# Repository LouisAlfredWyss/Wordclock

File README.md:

# Wordclock

Description and code of my Swiss-German Wordclock.

This project uses a Raspberry Pi to control a matrix of 121 WS281x LEDs (NeoPixels). It displays the current time using illuminated words in Swiss-German dialect (e.g., "Es isch viertel vor drüü").

The repository contains the Python code required to drive the LED matrix, as well as the mechanical and electrical files needed to physically build the clock (PCB layouts and laser cutting templates in the `mechanics/` folder).

## Hardware
* Raspberry Pi
* WS281x LED Strip (121 LEDs)
* Custom PCB and laser-cut casing

## Requirements
The project relies on the `rpi_ws281x` and `numpy` Python libraries.

```bash
sudo pip3 install rpi_ws281x numpy
```

## Running the Application
The `rpi_ws281x` library uses PWM via GPIO pin 18 by default, which requires root privileges.

To run the clock, execute the script in the `src/` folder:

```bash
sudo python3 src/main.py
```

### Options
* `-c` or `--clear`: Clears the LED display when the script exits (e.g., via Ctrl+C).

```bash
sudo python3 src/main.py -c
```

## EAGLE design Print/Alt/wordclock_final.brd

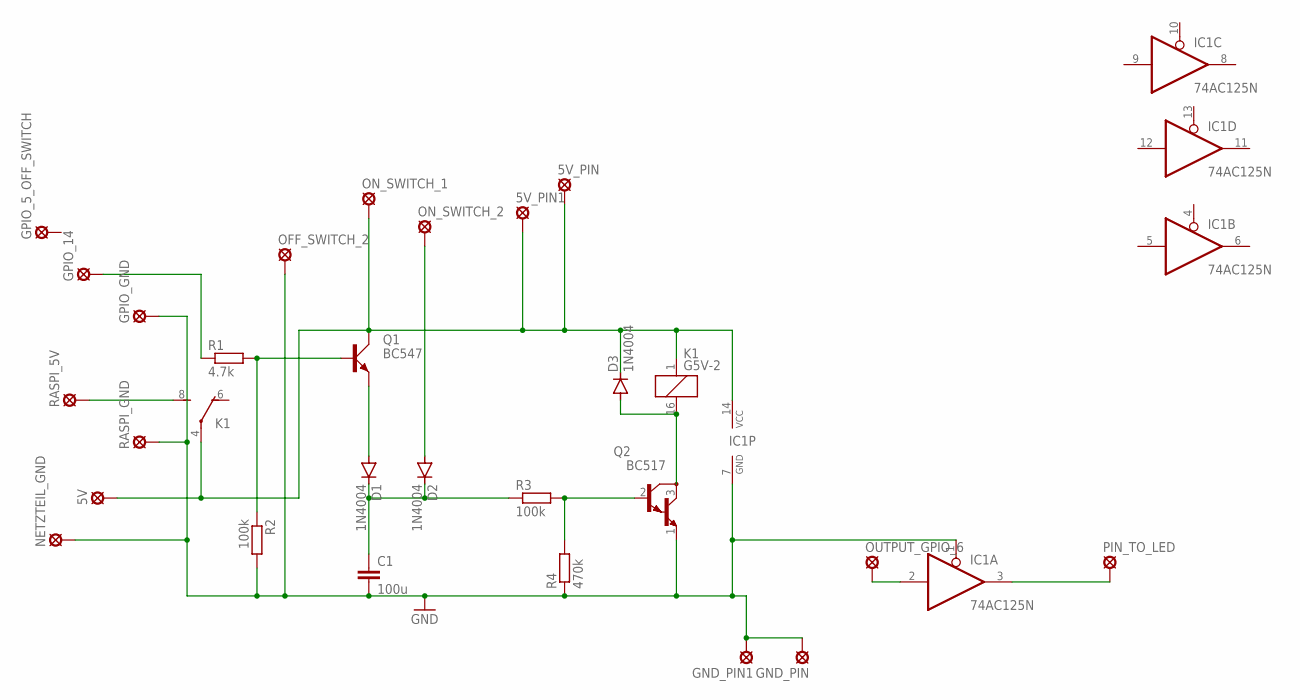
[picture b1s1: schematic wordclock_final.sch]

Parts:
5V, 5V_PIN, 5V_PIN1: SE14
C1: 100u; C025-060X050
D1, D2, D3: 1N4004; DO41-10
GND_PIN, GND_PIN1: SE14
GPIO_5_OFF_SWITCH, GPIO_14: SE14
GPIO_GND: SE14
IC1: 74AC125N; DIL14
K1: G5V-2
NETZTEIL_GND: SE14
OFF_SWITCH_2: SE14
ON_SWITCH_1, ON_SWITCH_2: SE14
OUTPUT_GPIO_6: SE14
PIN_TO_LED: SE14
Q1: BC547; SOT54A
Q2: BC517; TO92
R1: 4.7k; 0207/10
R2, R3: 100k; 0207/10
R4: 470k; 0207/10
RASPI_5V: SE14
RASPI_GND: SE14

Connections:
GND: C1.2, GND_PIN.MP, GND_PIN1.MP, GPIO_GND.MP, IC1.1 (OE), IC1.7 (GND), NETZTEIL_GND.MP, OFF_SWITCH_2.MP, Q2.1 (E), R2.2, R4.1, RASPI_GND.MP
unnamed: Q1.B, R1.2, R2.1
unnamed: D1.A, Q1.E
unnamed: D2.A, ON_SWITCH_2.MP
unnamed: IC1.2 (I), OUTPUT_GPIO_6.MP
unnamed: Q2.2 (B), R3.2, R4.2
unnamed: D3.A, K1.16 (2), Q2.3 (C)
unnamed: 5V.MP, 5V_PIN.MP, 5V_PIN1.MP, D3.C, IC1.14 (VCC), K1.1, K1.4, ON_SWITCH_1.MP, Q1.C
unnamed: C1.1, D1.C, D2.C, R3.1
unnamed: GPIO_14.MP, R1.1
unnamed: K1.8 (S), RASPI_5V.MP
unnamed: IC1.3 (O), PIN_TO_LED.MP

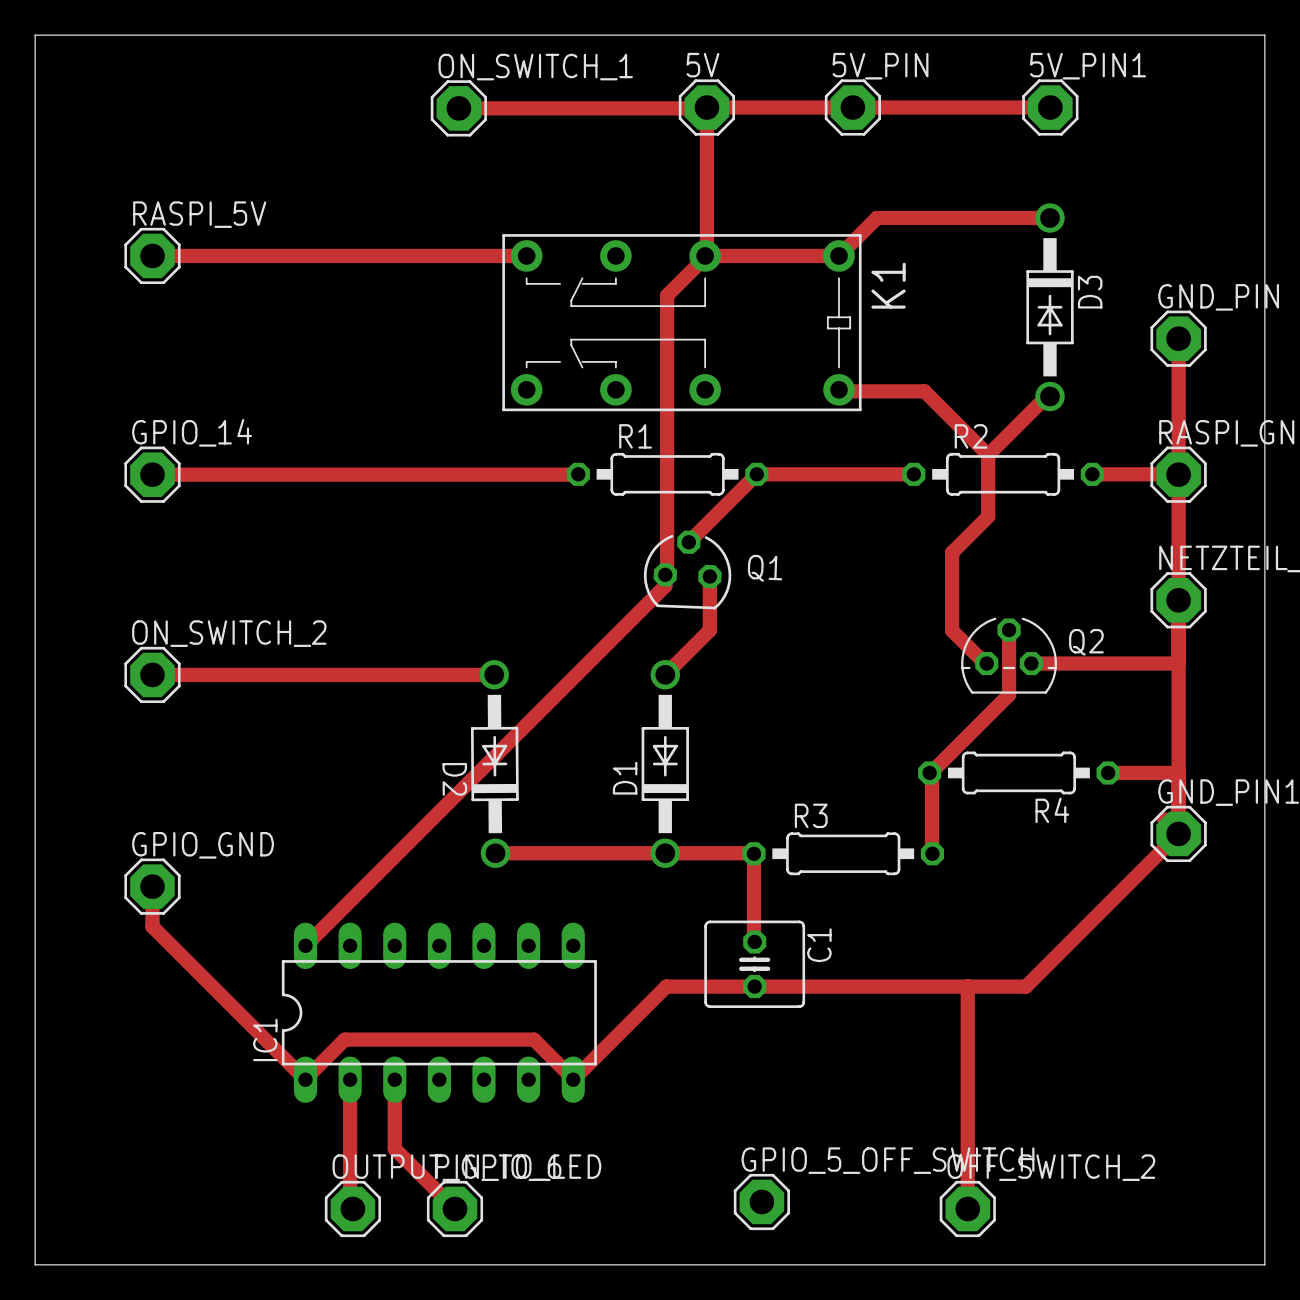
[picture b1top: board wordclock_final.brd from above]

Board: 2 copper layers, 70.0 x 70.0 mm, 28 parts (0 on the bottom side), 12 nets.

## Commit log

2023-06-23 First version of wordclock
2023-06-23 Materialliste erstellt
2023-06-23 Reorganize and write proper doc
2023-07-27 Completly new version with API request to get temperature from mystrom switchs
2025-01-27 feature: Added .gitignore file
2025-01-28 feature: organised folder structer new
2025-01-28 feature: Fixed code and clock is working again
2025-03-11 Corrected mistake when time was :25
2026-05-02 FIX: AttributeError
2026-05-02 FIX: Fix network issue
2026-05-02 FIX: Fixed ctrl+c error
2026-05-04 PERF/FIX: Optimize performance and fix flickering bug
    - Fix 'vor' flickering at 11:45 by properly handling minute 0
    - Reduce CPU usage by adding sleep in main loops
    - Fix strip.show() hardware spamming by moving out of clear loops
    - Throttle MyStrom API polling to prevent SD card wear
    - Update pandas json_normalize to fix deprecation warning
2026-05-04 FIX: Add missing 'halbi' when the time is 'füf über halbi'
2026-05-04 REFACTOR: Remove MyStrom functionality from Wordclock
    - Deleted mystrom.py as it will become a separate project
    - Removed corresponding variables, imports, and loops from main.py
2026-05-04 CHORE: Clean up dead code and documentation related to MyStrom
2026-05-04 DOCS: Expand README.md to describe project scope and installation
2026-05-06 feat: Add sleep mode and nighttime dimming
2026-05-06 chore: ignore GEMINI.md
2026-05-06 Fixes
2026-05-06 FIX: The Fix: I have applied a targeted patch to minute_set() in wordclock.py to prevent it from clearing the previous interval specifically when transitioning into the 35–39 minute block (minutes //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
2026-05-08 REFACTOR: Consolidate codebase to src/ directory
    - Removed duplicate/legacy main.py and wordclock.py from the root directory.
    - Updated README.md to reflect that the script should now be run from src/main.py.
